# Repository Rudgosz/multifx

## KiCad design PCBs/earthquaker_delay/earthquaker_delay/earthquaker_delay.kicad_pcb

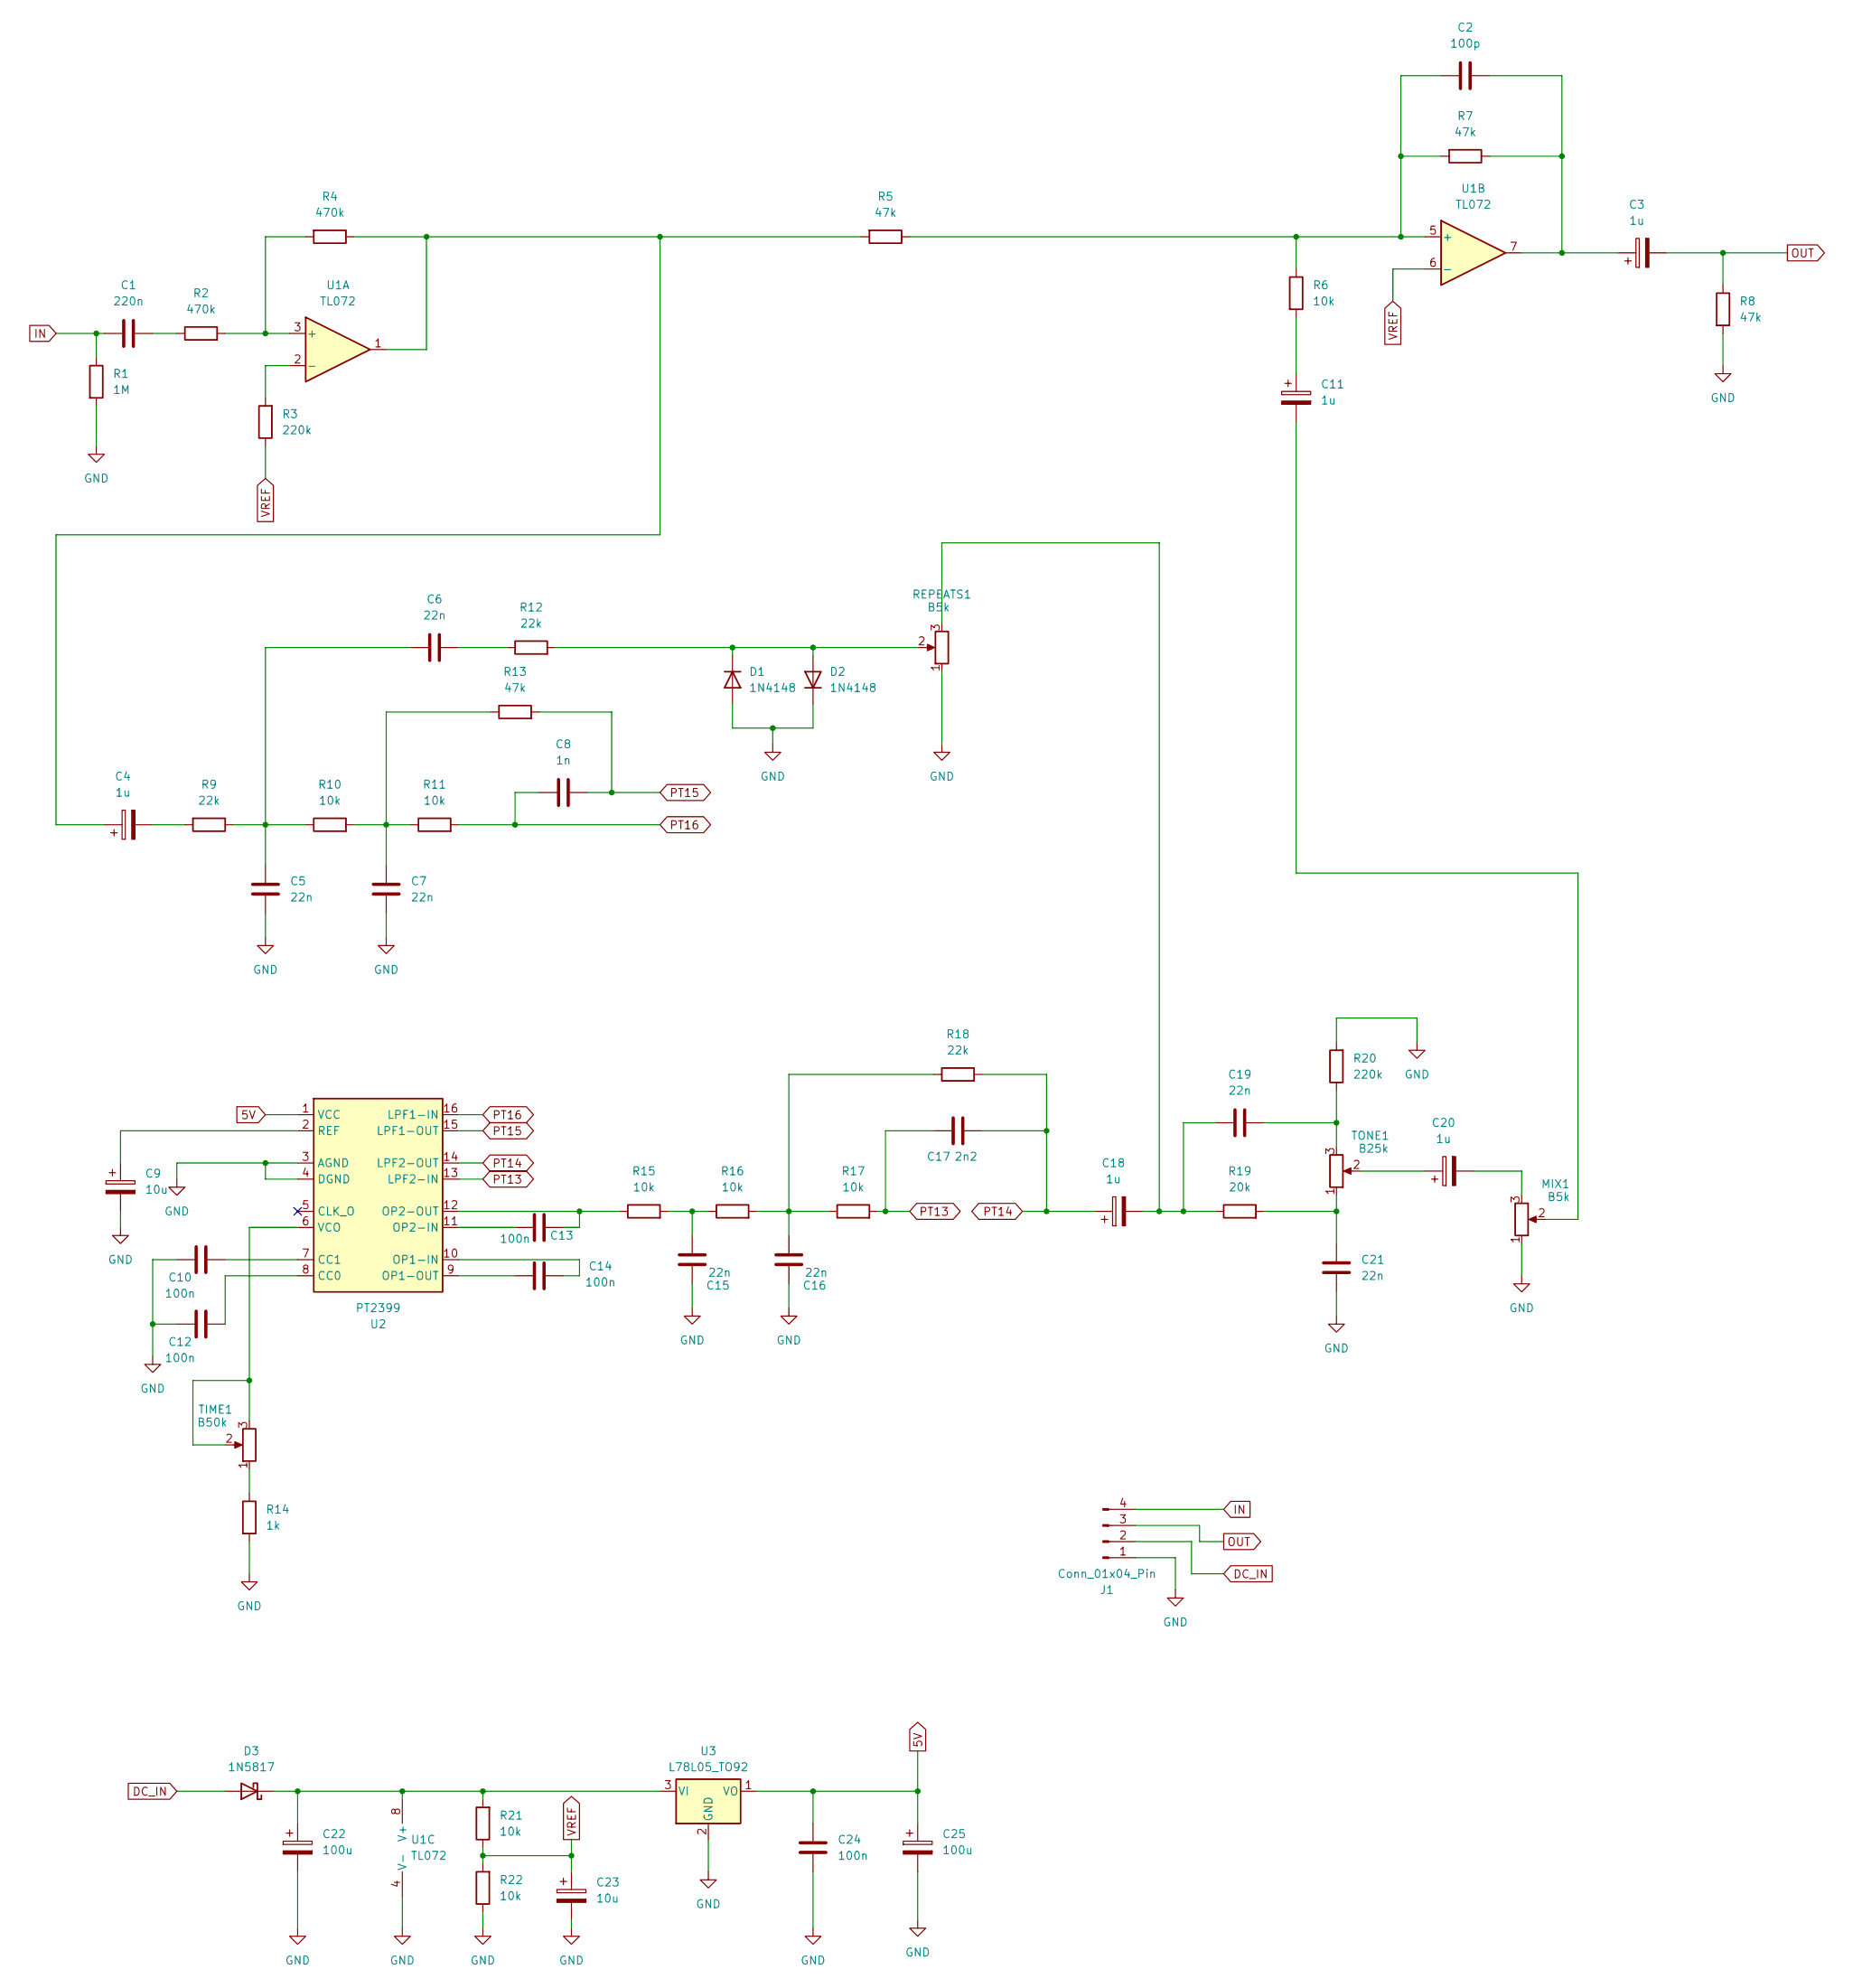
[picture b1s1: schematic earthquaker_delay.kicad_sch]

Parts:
C1: 220n; C_Disc_D5.0mm_W2.5mm_P5.00mm
C2: 100p; C_Disc_D5.0mm_W2.5mm_P5.00mm
C3, C4, C11, C18, C20: 1u; CP_Radial_D6.3mm_P2.50mm
C5, C6, C7, C15, C16, C19, C21: 22n; C_Disc_D5.0mm_W2.5mm_P5.00mm
C8: 1n; C_Disc_D5.0mm_W2.5mm_P5.00mm
C9, C23: 10u; CP_Radial_D6.3mm_P2.50mm
C10, C12, C13, C14, C24: 100n; C_Disc_D5.0mm_W2.5mm_P5.00mm
C17: 2n2; C_Disc_D5.0mm_W2.5mm_P5.00mm
C22, C25: 100u; CP_Radial_D6.3mm_P2.50mm
D1, D2: 1N4148; D_DO-35_SOD27_P7.62mm_Horizontal
D3: 1N5817; D_DO-41_SOD81_P10.16mm_Horizontal
J1: Conn_01x04_Pin; JST_XH_B4B-XH-A_1x04_P2.50mm_Vertical
MIX1: B5k; potentiometer_16_5_small_common
R1: 1M; R_Axial_DIN0204_L3.6mm_D1.6mm_P7.62mm_Horizontal
R2, R4: 470k; R_Axial_DIN0204_L3.6mm_D1.6mm_P7.62mm_Horizontal
R3, R20: 220k; R_Axial_DIN0204_L3.6mm_D1.6mm_P7.62mm_Horizontal
R5, R7, R8, R13: 47k; R_Axial_DIN0204_L3.6mm_D1.6mm_P7.62mm_Horizontal
R6, R10, R11, R15, R16, R17, R21, R22: 10k; R_Axial_DIN0204_L3.6mm_D1.6mm_P7.62mm_Horizontal
R9, R12, R18: 22k; R_Axial_DIN0204_L3.6mm_D1.6mm_P7.62mm_Horizontal
R14: 1k; R_Axial_DIN0204_L3.6mm_D1.6mm_P7.62mm_Horizontal
R19: 20k; R_Axial_DIN0204_L3.6mm_D1.6mm_P7.62mm_Horizontal
REPEATS1: B5k; potentiometer_16_5_small_common
TIME1: B50k; potentiometer_16_5_small_common
TONE1: B25k; potentiometer_16_5_small_common
U1: TL072; CERDIP-8_W7.62mm_SideBrazed_LongPads_Socket
U2: PT2399; DIP-16_W7.62mm
U3: L78L05_TO92; TO-92_Inline

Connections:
5V: C24.1, C25.1, U2.1 (VCC), U3.1 (VO)
DC_IN: D3.2 (A), J1.2
GND: C5.1, C7.1, C9.2, C10.1, C12.1, C15.1, C16.1, C21.2, C22.2, C23.2, C24.2, C25.2, D1.2 (A), D2.1 (K), J1.1, MIX1.1, R1.2, R8.2, R14.2, R20.2, R22.1, REPEATS1.1, U1.4 (V-), U2.3 (AGND), U2.4 (DGND), U3.2 (GND)
IN: C1.1, J1.4, R1.1
unnamed: C1.2, R2.1
unnamed: C2.2, C3.1, R7.1, U1.7
unnamed: C4.1, R4.1, R5.2, U1.1
unnamed: C4.2, R9.2
unnamed: C5.2, C6.2, R9.1, R10.1
unnamed: C6.1, R12.1
unnamed: C7.2, R10.2, R11.1, R13.1
unnamed: C11.1, R6.2
unnamed: C11.2, MIX1.2
unnamed: C15.2, R15.2, R16.1
unnamed: C16.2, R16.2, R17.1, R18.1
unnamed: C18.2, C19.2, R19.1, REPEATS1.3
unnamed: C19.1, R20.1, TONE1.3
unnamed: C20.1, TONE1.2
unnamed: C20.2, MIX1.3
unnamed: C21.1, R19.2, TONE1.1
unnamed: D1.1 (K), D2.2 (A), R12.2, REPEATS1.2
unnamed: C22.1, D3.1 (K), R21.2, U1.8 (V+), U3.3 (VI)
unnamed: R14.1, TIME1.1
unnamed: R2.2, R4.2, U1.3 (+)
unnamed: R3.2, U1.2 (-)
unnamed: C2.1, R5.1, R6.1, R7.2, U1.5 (+)
unnamed: C12.2, U2.8 (CC0)
unnamed: C10.2, U2.7 (CC1)
unnamed: C14.2, U2.10 (OP1-IN)
unnamed: C14.1, U2.9 (OP1-OUT)
unnamed: C13.1, U2.11 (OP2-IN)
unnamed: C13.2, R15.1, U2.12 (OP2-OUT)
unnamed: C9.1, U2.2 (REF)
unnamed: TIME1.2, TIME1.3, U2.6 (VCO)
OUT: C3.2, J1.3, R8.1
PT13: C17.1, R17.2, U2.13 (LPF2-IN)
PT14: C17.2, C18.1, R18.2, U2.14 (LPF2-OUT)
PT15: C8.1, R13.2, U2.15 (LPF1-OUT)
PT16: C8.2, R11.2, U2.16 (LPF1-IN)
VREF: C23.1, R3.1, R21.1, R22.2, U1.6 (-)

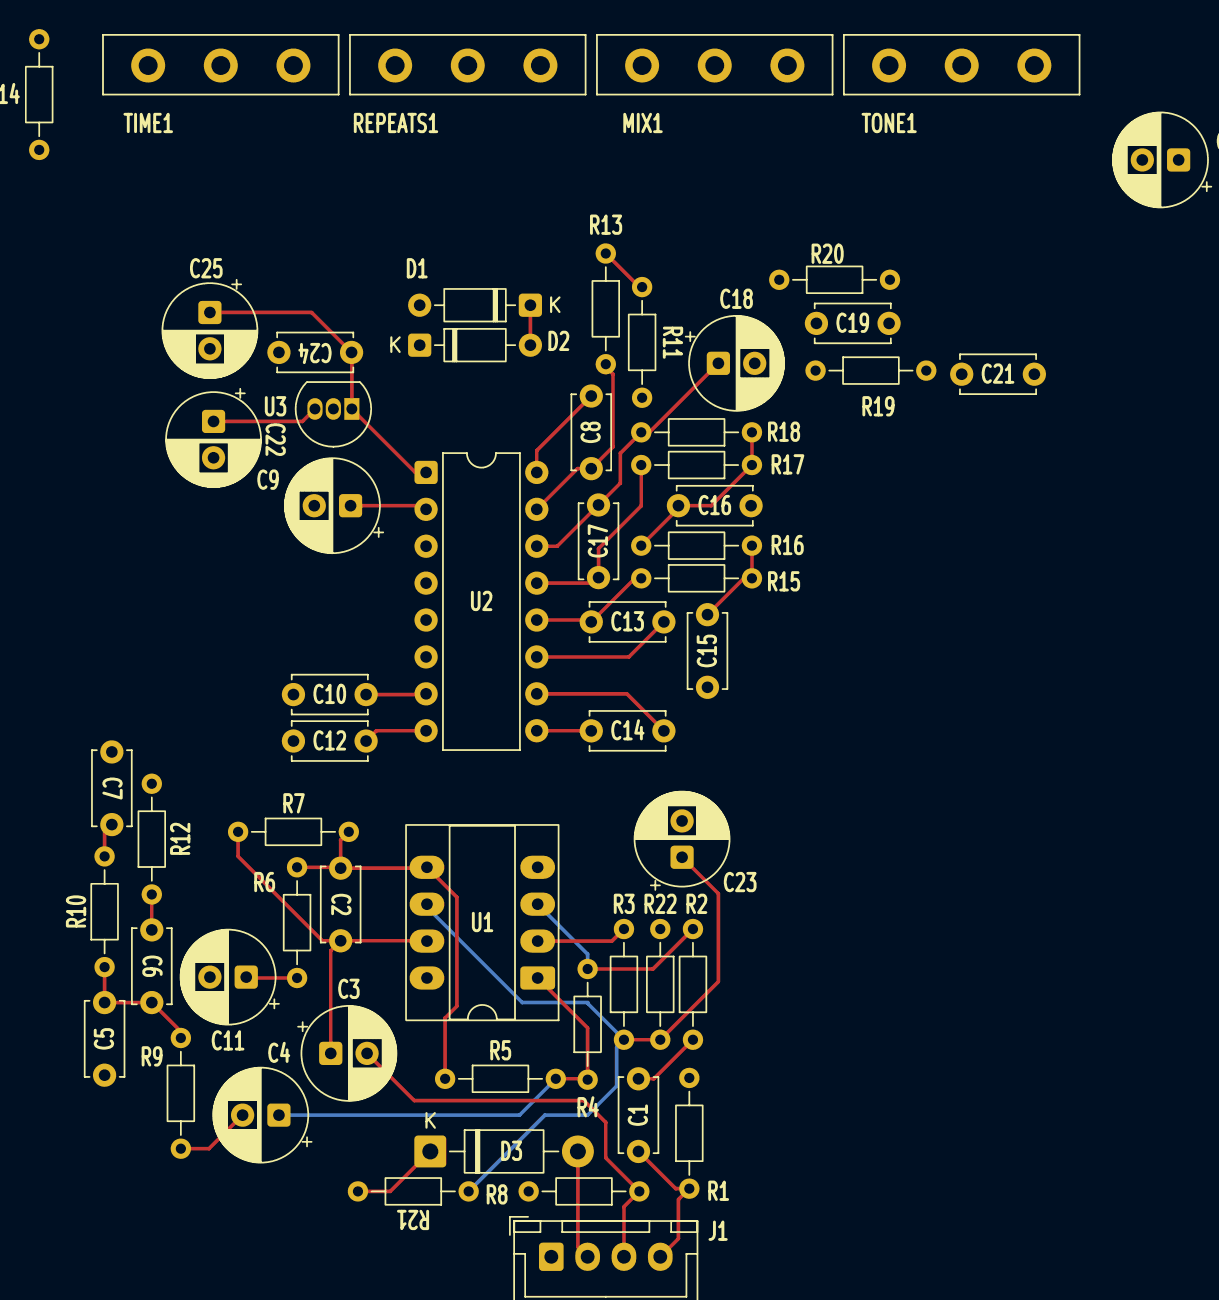
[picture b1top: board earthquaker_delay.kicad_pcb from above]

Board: 2 copper layers, 58 parts (0 on the bottom side), 40 nets.

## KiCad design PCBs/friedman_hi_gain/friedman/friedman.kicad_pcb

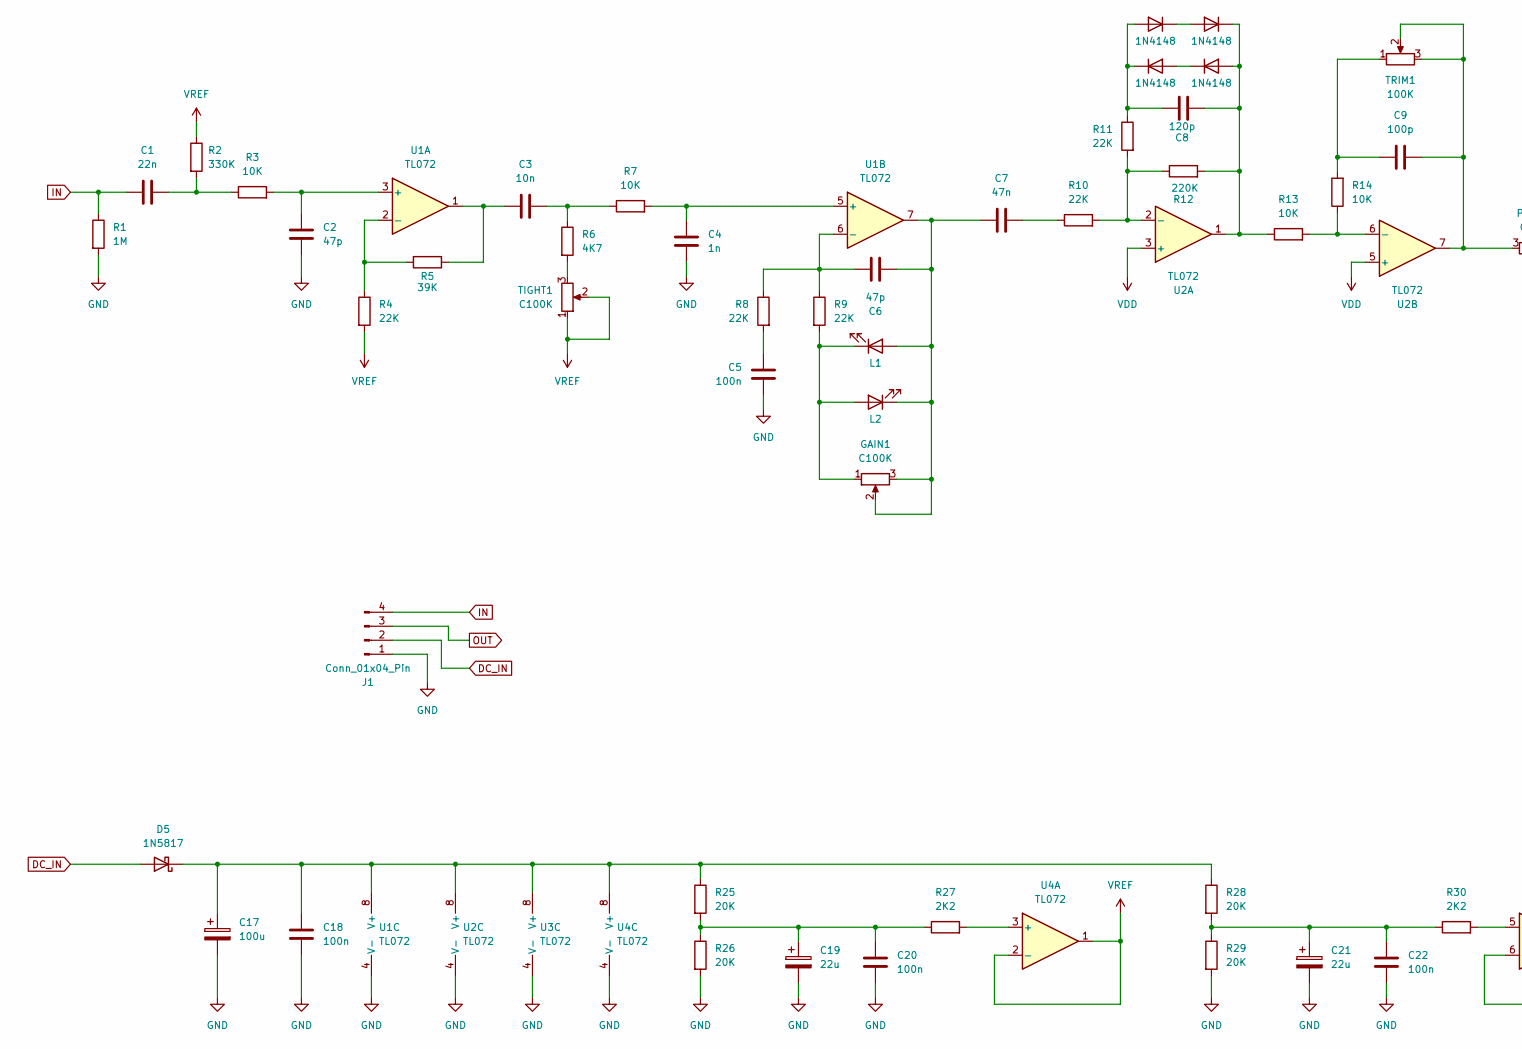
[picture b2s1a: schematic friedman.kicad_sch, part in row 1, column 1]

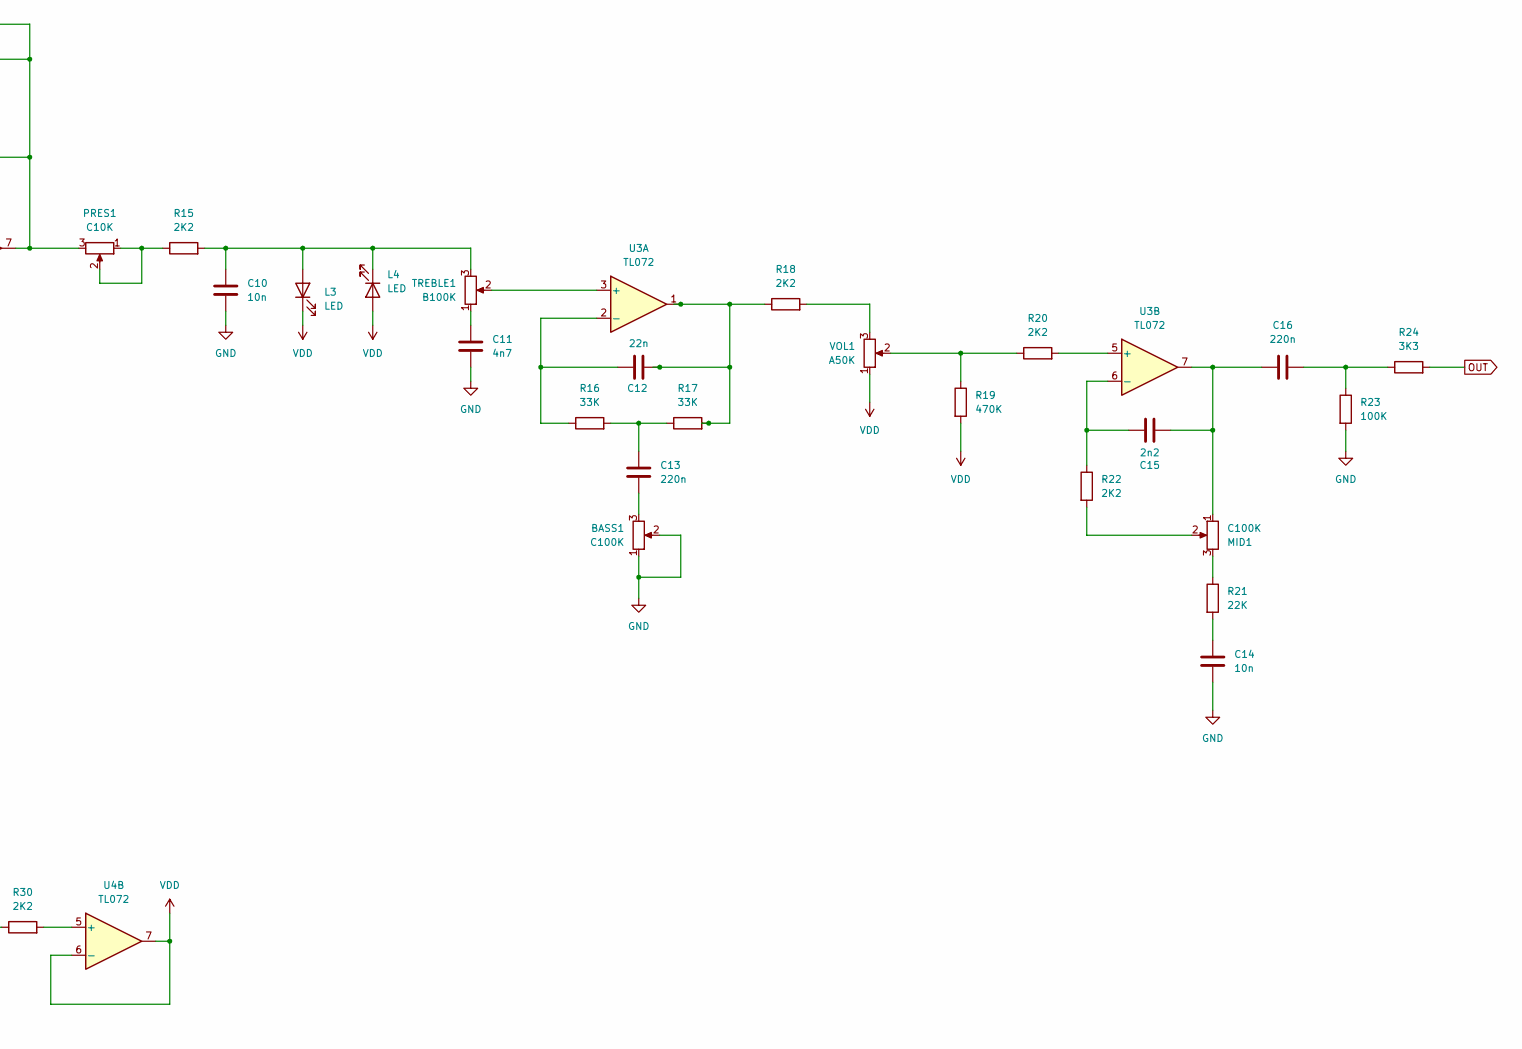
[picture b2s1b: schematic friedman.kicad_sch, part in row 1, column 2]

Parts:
BASS1: C100K; potentiometer_16_5_small_common
C1, C12: 22n; C_0805_2012Metric_Pad1.18x1.45mm_HandSolder
C2, C6: 47p; C_0805_2012Metric_Pad1.18x1.45mm_HandSolder
C3, C10, C14: 10n; C_0805_2012Metric_Pad1.18x1.45mm_HandSolder
C4: 1n; C_0805_2012Metric_Pad1.18x1.45mm_HandSolder
C5, C18, C20, C22: 100n; C_0805_2012Metric_Pad1.18x1.45mm_HandSolder
C7: 47n; C_0805_2012Metric_Pad1.18x1.45mm_HandSolder
C8: 120p; C_0805_2012Metric_Pad1.18x1.45mm_HandSolder
C9: 100p; C_0805_2012Metric_Pad1.18x1.45mm_HandSolder
C11: 4n7; C_0805_2012Metric_Pad1.18x1.45mm_HandSolder
C13, C16: 220n; C_0805_2012Metric_Pad1.18x1.45mm_HandSolder
C15: 2n2; C_0805_2012Metric_Pad1.18x1.45mm_HandSolder
C17: 100u; C_Radial_D10.0mm_H20.0mm_P5.00mm
C19, C21: 22u; C_Radial_D10.0mm_H20.0mm_P5.00mm
D1, D2, D3, D4: 1N4148; PinHeader_1x02_P2.54mm_Vertical
D5: 1N5817; D_DO-41_SOD81_P10.16mm_Horizontal
GAIN1: C100K; potentiometer_16_5_small_common
J1: Conn_01x04_Pin; JST_XH_B4B-XH-A_1x04_P2.50mm_Vertical
L1, L2, L3, L4: LED; PinHeader_1x02_P2.54mm_Vertical
MID1: C100K; potentiometer_16_5_small_common
PRES1: C10K; potentiometer_16_5_small_common
R1: 1M; R_0805_2012Metric_Pad1.20x1.40mm_HandSolder
R2: 330K; R_0805_2012Metric_Pad1.20x1.40mm_HandSolder
R3, R7, R13, R14: 10K; R_0805_2012Metric_Pad1.20x1.40mm_HandSolder
R4, R8, R9, R10, R11, R21: 22K; R_0805_2012Metric_Pad1.20x1.40mm_HandSolder
R5: 39K; R_0603_1608Metric_Pad0.98x0.95mm_HandSolder
R6: 4K7; R_0805_2012Metric_Pad1.20x1.40mm_HandSolder
R12: 220K; R_0805_2012Metric_Pad1.20x1.40mm_HandSolder
R15, R18, R20, R22, R27, R30: 2K2; R_0805_2012Metric_Pad1.20x1.40mm_HandSolder
R16, R17: 33K; R_0805_2012Metric_Pad1.20x1.40mm_HandSolder
R19: 470K; R_0805_2012Metric_Pad1.20x1.40mm_HandSolder
R23: 100K; R_0805_2012Metric_Pad1.20x1.40mm_HandSolder
R24: 3K3; R_0805_2012Metric_Pad1.20x1.40mm_HandSolder
R25, R26, R28, R29: 20K; R_0805_2012Metric_Pad1.20x1.40mm_HandSolder
TIGHT1: C100K; potentiometer_16_5_small_common
TREBLE1: B100K; potentiometer_16_5_small_common
TRIM1: 100K; Potentiometer_Runtron_RM-065_Vertical
U1, U2, U3, U4: TL072; CERDIP-8_W7.62mm_SideBrazed_LongPads_Socket
VOL1: A50K; potentiometer_16_5_small_common

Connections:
DC_IN: D5.2 (A), J1.2
GND: BASS1.1, BASS1.2, C2.2, C4.2, C5.2, C10.2, C11.2, C14.2, C17.2, C18.2, C19.2, C20.2, C21.2, C22.2, J1.1, R1.2, R23.2, R26.2, R29.2, U1.4 (V-), U2.4 (V-), U3.4 (V-), U4.4 (V-)
IN: C1.1, J1.4, R1.1
unnamed: BASS1.3, C13.2
unnamed: C1.2, R2.2, R3.1
unnamed: C3.1, R5.1, U1.1
unnamed: C3.2, R6.1, R7.1
unnamed: C5.1, R8.2
unnamed: C7.2, R10.1
unnamed: C9.1, R14.2, TRIM1.1
unnamed: C9.2, PRES1.3, TRIM1.2, TRIM1.3, U2.7
unnamed: C11.1, TREBLE1.1
unnamed: C12.2, R17.2, R18.1, U3.1
unnamed: C13.1, R16.2, R17.1
unnamed: C14.1, R21.2
unnamed: C15.2, C16.1, MID1.1, U3.7
unnamed: C16.2, R23.1, R24.1
unnamed: C19.1, C20.1, R25.2, R26.1, R27.1
unnamed: C21.1, C22.1, R28.2, R29.1, R30.1
unnamed: D1.2 (A), D2.1 (K)
unnamed: C8.1, D1.1 (K), D4.2 (A), R11.1
unnamed: C8.2, D2.2 (A), D3.1 (K), R12.2, R13.1, U2.1
unnamed: D3.2 (A), D4.1 (K)
unnamed: C17.1, C18.1, D5.1 (K), R25.1, R28.1, U1.8 (V+), U2.8 (V+), U3.8 (V+), U4.8 (V+)
unnamed: C6.2, C7.1, GAIN1.2, GAIN1.3, L1.2 (A), L2.1 (K), U1.7
unnamed: GAIN1.1, L1.1 (K), L2.2 (A), R9.2
unnamed: C10.1, L3.2 (A), L4.1 (K), R15.2, TREBLE1.3
unnamed: MID1.2, R22.2
unnamed: MID1.3, R21.1
unnamed: PRES1.1, PRES1.2, R15.1
unnamed: R6.2, TIGHT1.3
unnamed: R18.2, VOL1.3
unnamed: R19.1, R20.1, VOL1.2
unnamed: C2.1, R3.2, U1.3 (+)
unnamed: R4.1, R5.2, U1.2 (-)
unnamed: C4.1, R7.2, U1.5 (+)
unnamed: C6.1, R8.1, R9.1, U1.6 (-)
unnamed: R10.2, R11.2, R12.1, U2.2 (-)
unnamed: R13.2, R14.1, U2.6 (-)
unnamed: TREBLE1.2, U3.3 (+)
unnamed: C12.1, R16.1, U3.2 (-)
unnamed: R20.2, U3.5 (+)
unnamed: C15.1, R22.1, U3.6 (-)
unnamed: R27.2, U4.3 (+)
unnamed: R30.2, U4.5 (+)
OUT: J1.3, R24.2
VDD: L3.1 (K), L4.2 (A), R19.2, U2.3 (+), U2.5 (+), U4.6 (-), U4.7, VOL1.1
VREF: R2.1, R4.2, TIGHT1.1, TIGHT1.2, U4.1, U4.2 (-)

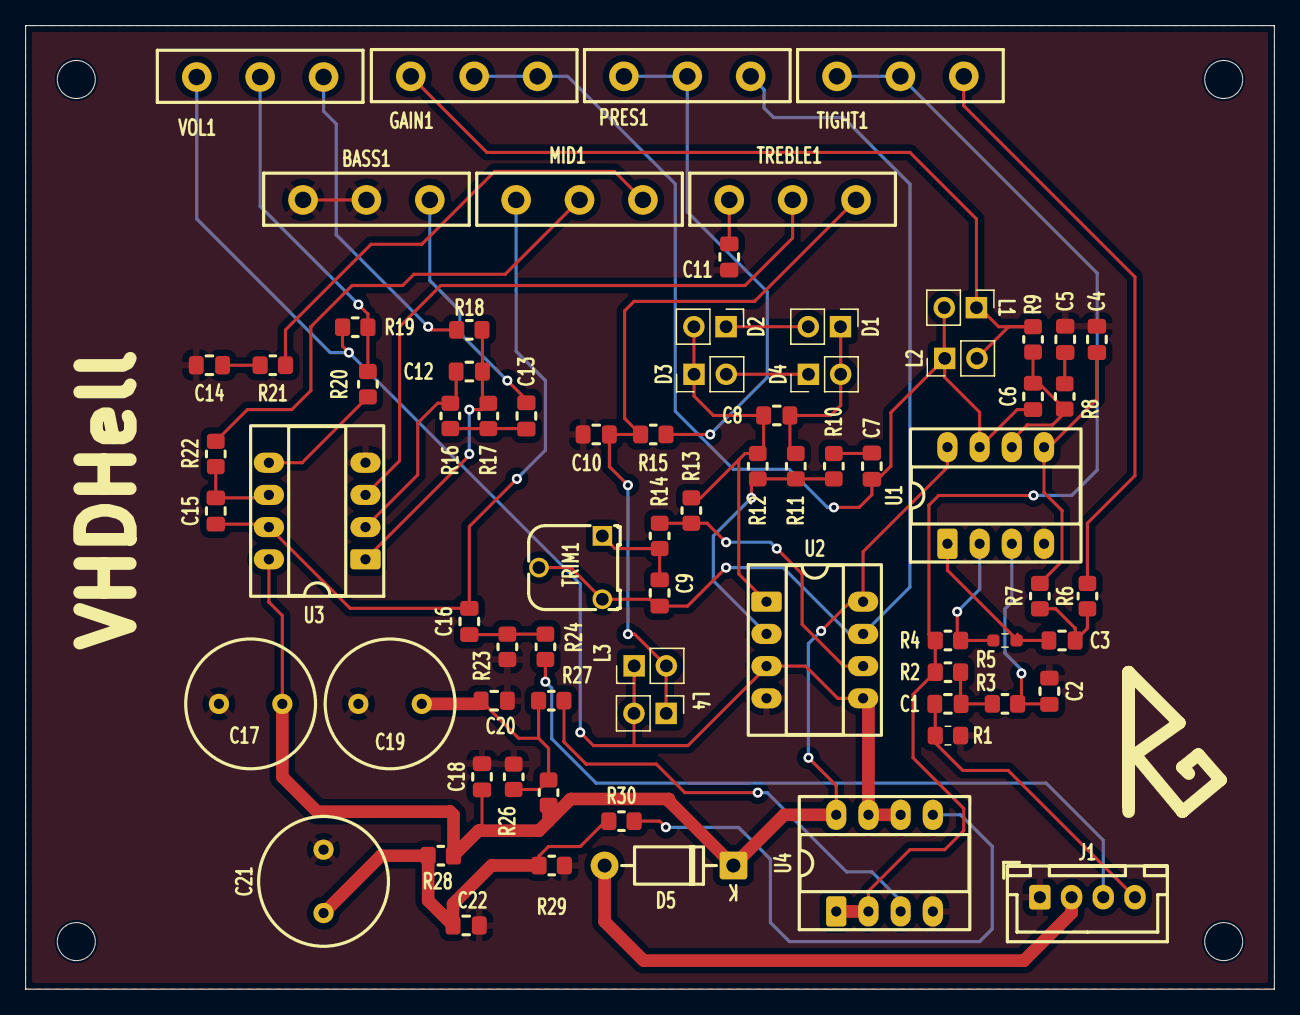
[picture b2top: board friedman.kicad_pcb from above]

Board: 2 copper layers, 98.5 x 76.0 mm, 78 parts (0 on the bottom side), 48 nets.

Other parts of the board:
REF1, REF2, REF3, REF4: MountingHole_3mm

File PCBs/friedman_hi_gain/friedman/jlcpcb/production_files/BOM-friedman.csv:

Comment,Designator,Footprint,LCSC,Quantity
47p,"C2,C6",C_0805_2012Metric_Pad1.18x1.45mm_HandSolder,C14857,2
100K,R23,R_0805_2012Metric_Pad1.20x1.40mm_HandSolder,C149504,1
10n,"C10,C14,C3",C_0805_2012Metric_Pad1.18x1.45mm_HandSolder,C1710,3
22n,"C1,C12",C_0805_2012Metric_Pad1.18x1.45mm_HandSolder,C1729,2
10K,"R13,R14,R3,R7",R_0805_2012Metric_Pad1.20x1.40mm_HandSolder,C17414,4
4n7,C11,C_0805_2012Metric_Pad1.18x1.45mm_HandSolder,C1744,1
1M,R1,R_0805_2012Metric_Pad1.20x1.40mm_HandSolder,C17514,1
2K2,"R15,R18,R20,R22,R27,R30",R_0805_2012Metric_Pad1.20x1.40mm_HandSolder,C17520,6
220K,R12,R_0805_2012Metric_Pad1.20x1.40mm_HandSolder,C17556,1
22K,"R10,R11,R21,R4,R8,R9",R_0805_2012Metric_Pad1.20x1.40mm_HandSolder,C17560,6
330K,R2,R_0805_2012Metric_Pad1.20x1.40mm_HandSolder,C17630,1
33K,"R16,R17",R_0805_2012Metric_Pad1.20x1.40mm_HandSolder,C17633,2
4K7,R6,R_0805_2012Metric_Pad1.20x1.40mm_HandSolder,C17673,1
470K,R19,R_0805_2012Metric_Pad1.20x1.40mm_HandSolder,C17709,1
100p,C9,C_0805_2012Metric_Pad1.18x1.45mm_HandSolder,C1790,1
39K,R5,R_0603_1608Metric_Pad0.98x0.95mm_HandSolder,C23153,1
3K3,R24,R_0805_2012Metric_Pad1.20x1.40mm_HandSolder,C26010,1
100n,"C18,C20,C22,C5",C_0805_2012Metric_Pad1.18x1.45mm_HandSolder,C28233,4
2n2,C15,C_0805_2012Metric_Pad1.18x1.45mm_HandSolder,C28260,1
20K,"R25,R26,R28,R29",R_0805_2012Metric_Pad1.20x1.40mm_HandSolder,C4328,4
1n,C4,C_0805_2012Metric_Pad1.18x1.45mm_HandSolder,C46653,1
47n,"C7,C8",C_0805_2012Metric_Pad1.18x1.45mm_HandSolder,C53134,2
220n,"C13,C16",C_0805_2012Metric_Pad1.18x1.45mm_HandSolder,C5378,2
1N4148,D3,PinHeader_1x02_P2.54mm_Vertical,,1
1N4148,D1,PinHeader_1x02_P2.54mm_Vertical,,1
A50K,VOL1,potentiometer_16_5_small_common,,1
LED,L4,PinHeader_1x02_P2.54mm_Vertical,,1
1N4148,D2,PinHeader_1x02_P2.54mm_Vertical,,1
1N4148,D4,PinHeader_1x02_P2.54mm_Vertical,,1
LED,L1,PinHeader_1x02_P2.54mm_Vertical,,1
TL072,U3,CERDIP-8_W7.62mm_SideBrazed_LongPads_Socket,,1
B100K,TREBLE1,potentiometer_16_5_small_common,,1
TL072,U4,CERDIP-8_W7.62mm_SideBrazed_LongPads_Socket,,1
TL072,U1,CERDIP-8_W7.62mm_SideBrazed_LongPads_Socket,,1
LED,L3,PinHeader_1x02_P2.54mm_Vertical,,1
1N5817,D5,D_DO-41_SOD81_P10.16mm_Horizontal,,1
22u,C21,C_Radial_D10.0mm_H20.0mm_P5.00mm,,1
C10K,PRES1,potentiometer_16_5_small_common,,1
Conn_01x04_Pin,J1,JST_XH_B4B-XH-A_1x04_P2.50mm_Vertical,,1
100K,TRIM1,Potentiometer_Runtron_RM-065_Vertical,,1
TL072,U2,CERDIP-8_W7.62mm_SideBrazed_LongPads_Socket,,1
C100K,GAIN1,potentiometer_16_5_small_common,,1
C100K,TIGHT1,potentiometer_16_5_small_common,,1
LED,L2,PinHeader_1x02_P2.54mm_Vertical,,1
100u,C17,C_Radial_D10.0mm_H20.0mm_P5.00mm,,1
C100K,MID1,potentiometer_16_5_small_common,,1
22u,C19,C_Radial_D10.0mm_H20.0mm_P5.00mm,,1
C100K,BASS1,potentiometer_16_5_small_common,,1

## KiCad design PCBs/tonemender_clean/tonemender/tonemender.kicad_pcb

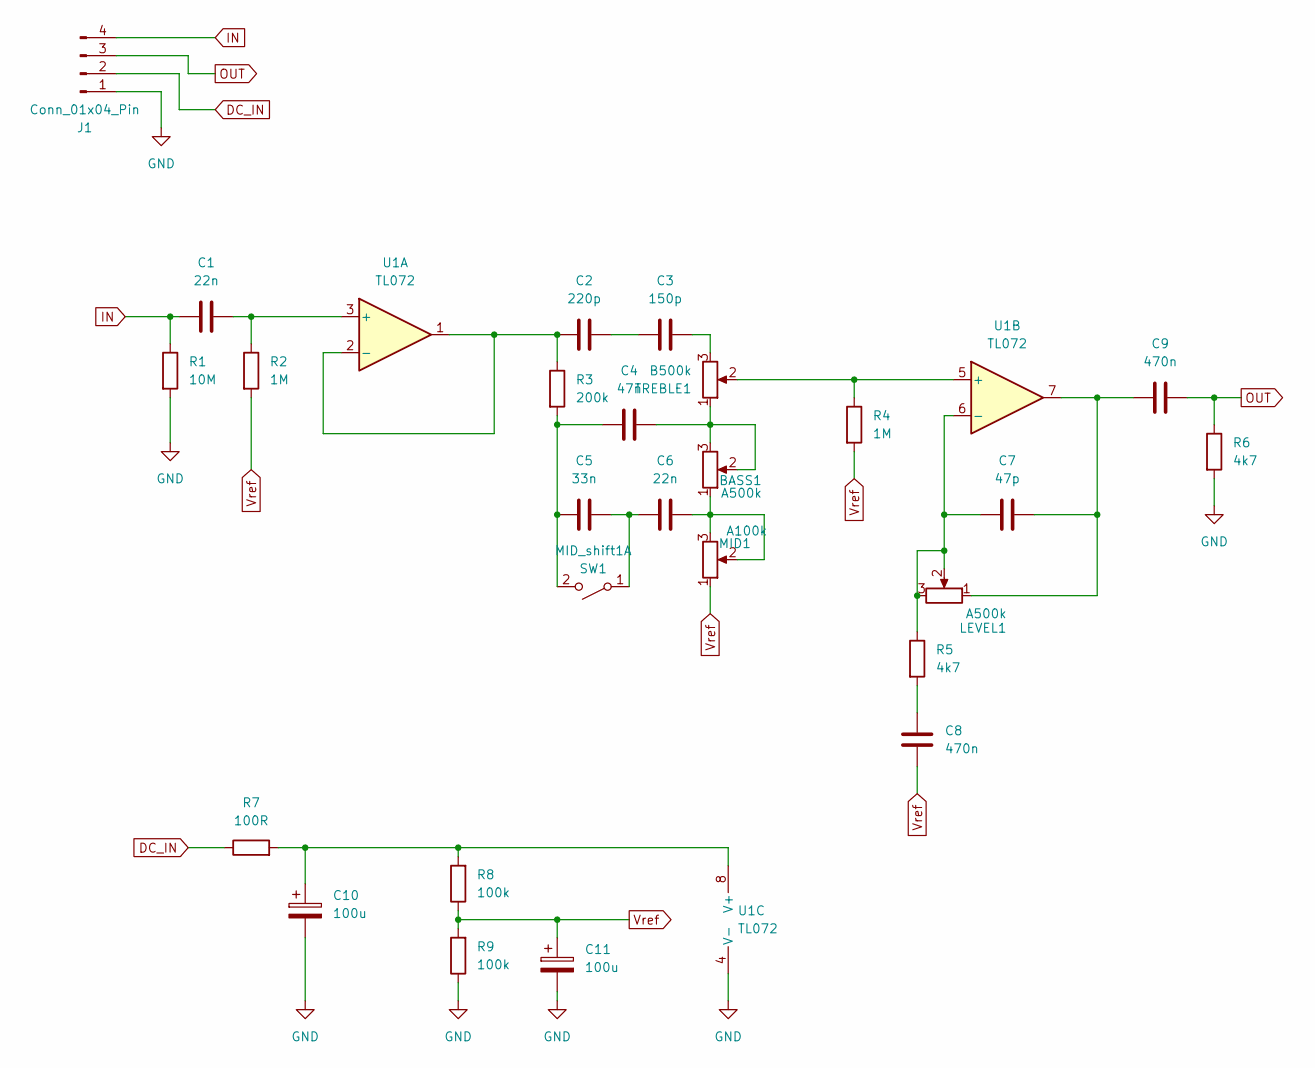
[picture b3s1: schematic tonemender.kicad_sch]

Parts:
BASS1: A500k; potentiometer_16_5_small_common
C1, C6: 22n; C_Disc_D5.0mm_W2.5mm_P5.00mm
C2: 220p; C_Disc_D5.0mm_W2.5mm_P5.00mm
C3: 150p; C_Disc_D5.0mm_W2.5mm_P5.00mm
C4: 47n; C_Disc_D5.0mm_W2.5mm_P5.00mm
C5: 33n; C_Disc_D5.0mm_W2.5mm_P5.00mm
C7: 47p; C_Disc_D5.0mm_W2.5mm_P5.00mm
C8, C9: 470n; C_Disc_D5.0mm_W2.5mm_P5.00mm
C10, C11: 100u; CP_Radial_D6.3mm_P2.50mm
J1: Conn_01x04_Pin; JST_XH_B4B-XH-A_1x04_P2.50mm_Vertical
LEVEL1: A500k; potentiometer_16_5_small_common
MID1: A100k; potentiometer_16_5_small_common
MID_shift1: SW1; PinHeader_1x02_P2.54mm_Vertical
R1: 10M; R_Axial_DIN0204_L3.6mm_D1.6mm_P7.62mm_Horizontal
R2, R4: 1M; R_Axial_DIN0204_L3.6mm_D1.6mm_P7.62mm_Horizontal
R3: 200k; R_Axial_DIN0204_L3.6mm_D1.6mm_P7.62mm_Horizontal
R5, R6: 4k7; R_Axial_DIN0204_L3.6mm_D1.6mm_P7.62mm_Horizontal
R7: 100R; R_Axial_DIN0204_L3.6mm_D1.6mm_P7.62mm_Horizontal
R8, R9: 100k; R_Axial_DIN0204_L3.6mm_D1.6mm_P7.62mm_Horizontal
TREBLE1: B500k; potentiometer_16_5_small_common
U1: TL072; DIP-8_W7.62mm_LongPads

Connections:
DC_IN: J1.2, R7.1
GND: C10.2, C11.2, J1.1, R1.2, R6.2, R9.1, U1.4 (V-)
IN: C1.1, J1.4, R1.1
unnamed: BASS1.1, C6.2, MID1.2, MID1.3
unnamed: BASS1.2, BASS1.3, C4.2, TREBLE1.1
unnamed: C2.2, C3.1
unnamed: C3.2, TREBLE1.3
unnamed: C7.2, C9.1, LEVEL1.1, U1.7
unnamed: C8.1, R5.2
unnamed: C5.2, C6.1, MID_shift1.1 (A)
unnamed: C4.1, C5.1, MID_shift1.2 (B), R3.2
unnamed: C1.2, R2.1, U1.3 (+)
unnamed: C2.1, R3.1, U1.1, U1.2 (-)
unnamed: R4.1, TREBLE1.2, U1.5 (+)
unnamed: C7.1, LEVEL1.2, LEVEL1.3, R5.1, U1.6 (-)
unnamed: C10.1, R7.2, R8.2, U1.8 (V+)
OUT: C9.2, J1.3, R6.1
Vref: C8.2, C11.1, MID1.1, R2.2, R4.2, R8.1, R9.2

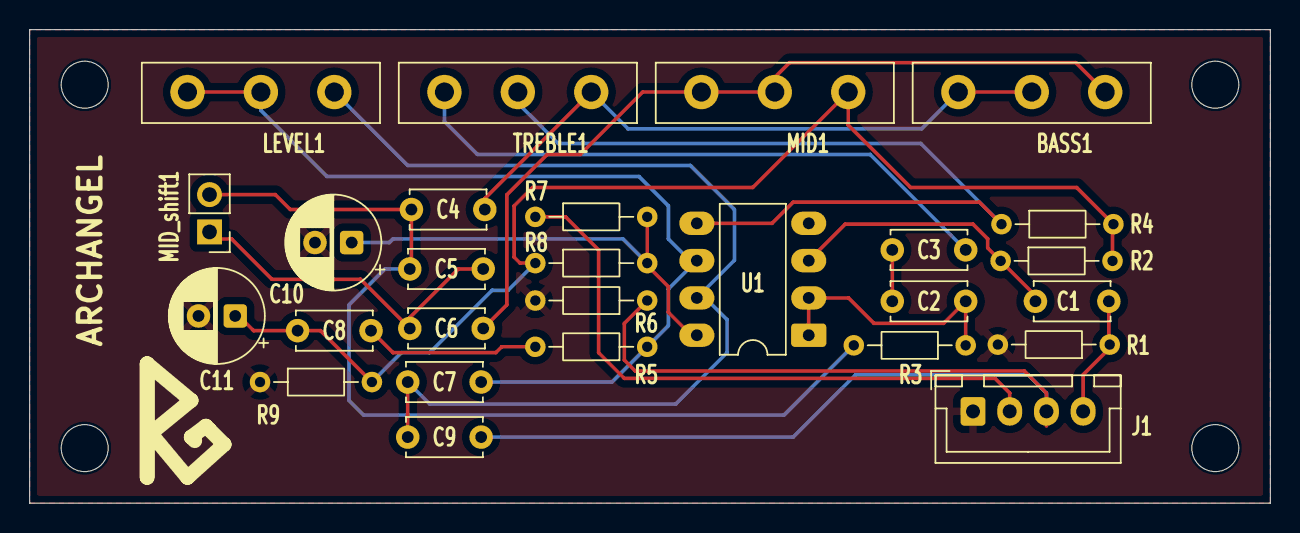
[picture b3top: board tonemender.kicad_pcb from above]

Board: 2 copper layers, 84.5 x 32.2 mm, 31 parts (0 on the bottom side), 18 nets.

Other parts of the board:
REF1, REF2, REF3, REF4: MountingHole_3.2mm_M3

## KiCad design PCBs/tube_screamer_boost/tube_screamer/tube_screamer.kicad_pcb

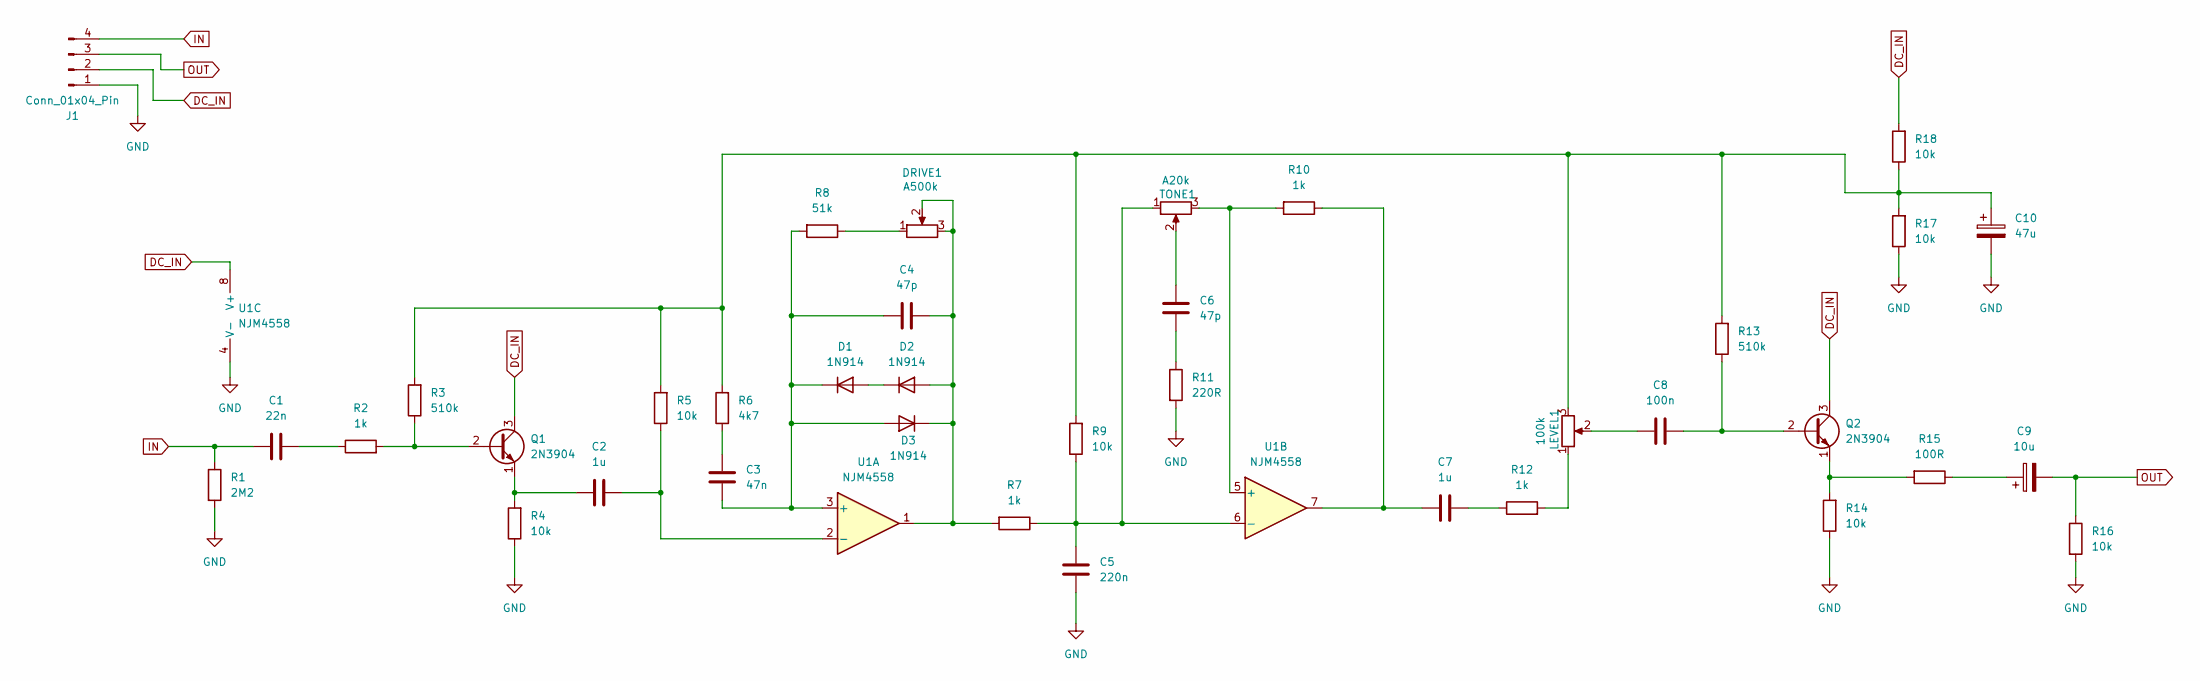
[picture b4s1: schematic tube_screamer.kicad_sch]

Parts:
C1: 22n; C_Disc_D5.0mm_W2.5mm_P5.00mm
C2, C7: 1u; C_Disc_D5.0mm_W2.5mm_P5.00mm
C3: 47n; C_Disc_D5.0mm_W2.5mm_P5.00mm
C4, C6: 47p; C_Disc_D5.0mm_W2.5mm_P5.00mm
C5: 220n; C_Disc_D5.0mm_W2.5mm_P5.00mm
C8: 100n; C_Disc_D5.0mm_W2.5mm_P5.00mm
C9: 10u; CP_Radial_D6.3mm_P2.50mm
C10: 47u; CP_Radial_D6.3mm_P2.50mm
D1, D2, D3: 1N914; D_A-405_P5.08mm_Vertical_AnodeUp
DRIVE1: A500k; potentiometer_16_5_small_common
J1: Conn_01x04_Pin; JST_XH_B4B-XH-A_1x04_P2.50mm_Vertical
LEVEL1: 100k; potentiometer_16_5_small_common
Q1, Q2: 2N3904; TO-92L_Wide
R1: 2M2; R_Axial_DIN0204_L3.6mm_D1.6mm_P7.62mm_Horizontal
R2, R7, R10, R12: 1k; R_Axial_DIN0204_L3.6mm_D1.6mm_P7.62mm_Horizontal
R3, R13: 510k; R_Axial_DIN0204_L3.6mm_D1.6mm_P7.62mm_Horizontal
R4, R5, R9, R14, R16, R17, R18: 10k; R_Axial_DIN0204_L3.6mm_D1.6mm_P7.62mm_Horizontal
R6: 4k7; R_Axial_DIN0204_L3.6mm_D1.6mm_P7.62mm_Horizontal
R8: 51k; R_Axial_DIN0204_L3.6mm_D1.6mm_P7.62mm_Horizontal
R11: 220R; R_Axial_DIN0204_L3.6mm_D1.6mm_P7.62mm_Horizontal
R15: 100R; R_Axial_DIN0204_L3.6mm_D1.6mm_P7.62mm_Horizontal
TONE1: A20k; potentiometer_16_5_small_common
U1: NJM4558; DIP-8_W7.62mm_LongPads

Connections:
DC_IN: J1.2, Q1.3 (C), Q2.3 (C), R18.2, U1.8 (V+)
GND: C5.1, C10.2, J1.1, R1.2, R4.1, R11.2, R14.1, R16.2, R17.1, U1.4 (V-)
IN: C1.1, J1.4, R1.1
unnamed: C1.2, R2.1
unnamed: C3.2, R6.1
unnamed: C6.1, R11.1
unnamed: C6.2, TONE1.2
unnamed: C7.1, R12.1
unnamed: C7.2, R10.1, U1.7
unnamed: C8.2, LEVEL1.2
unnamed: C9.1, R15.1
unnamed: C10.1, LEVEL1.3, R3.2, R5.2, R6.2, R9.2, R13.2, R17.2, R18.1
unnamed: D1.2 (A), D2.1 (K)
unnamed: C3.1, C4.1, D1.1 (K), D3.2 (A), R8.2, U1.3 (+)
unnamed: C4.2, D2.2 (A), D3.1 (K), DRIVE1.2, DRIVE1.3, R7.2, U1.1
unnamed: DRIVE1.1, R8.1
unnamed: LEVEL1.1, R12.2
unnamed: Q1.2 (B), R2.2, R3.1
unnamed: C2.1, Q1.1 (E), R4.2
unnamed: C8.1, Q2.2 (B), R13.1
unnamed: Q2.1 (E), R14.2, R15.2
unnamed: C2.2, R5.1, U1.2 (-)
unnamed: R10.2, TONE1.3, U1.5 (+)
unnamed: C5.2, R7.1, R9.1, TONE1.1, U1.6 (-)
OUT: C9.2, J1.3, R16.1
